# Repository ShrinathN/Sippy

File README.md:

# Sippy
A device which will remind me to drink water. Pretty cool. Uses accelerometer data to predict when, and how much water was drank. Needs the geometry of the bottle it is mounted on to work. WIP.

## Assembled

## Images of the board

## Images of the enclosure

## Renders of the PCB

## Renders of the enclosure

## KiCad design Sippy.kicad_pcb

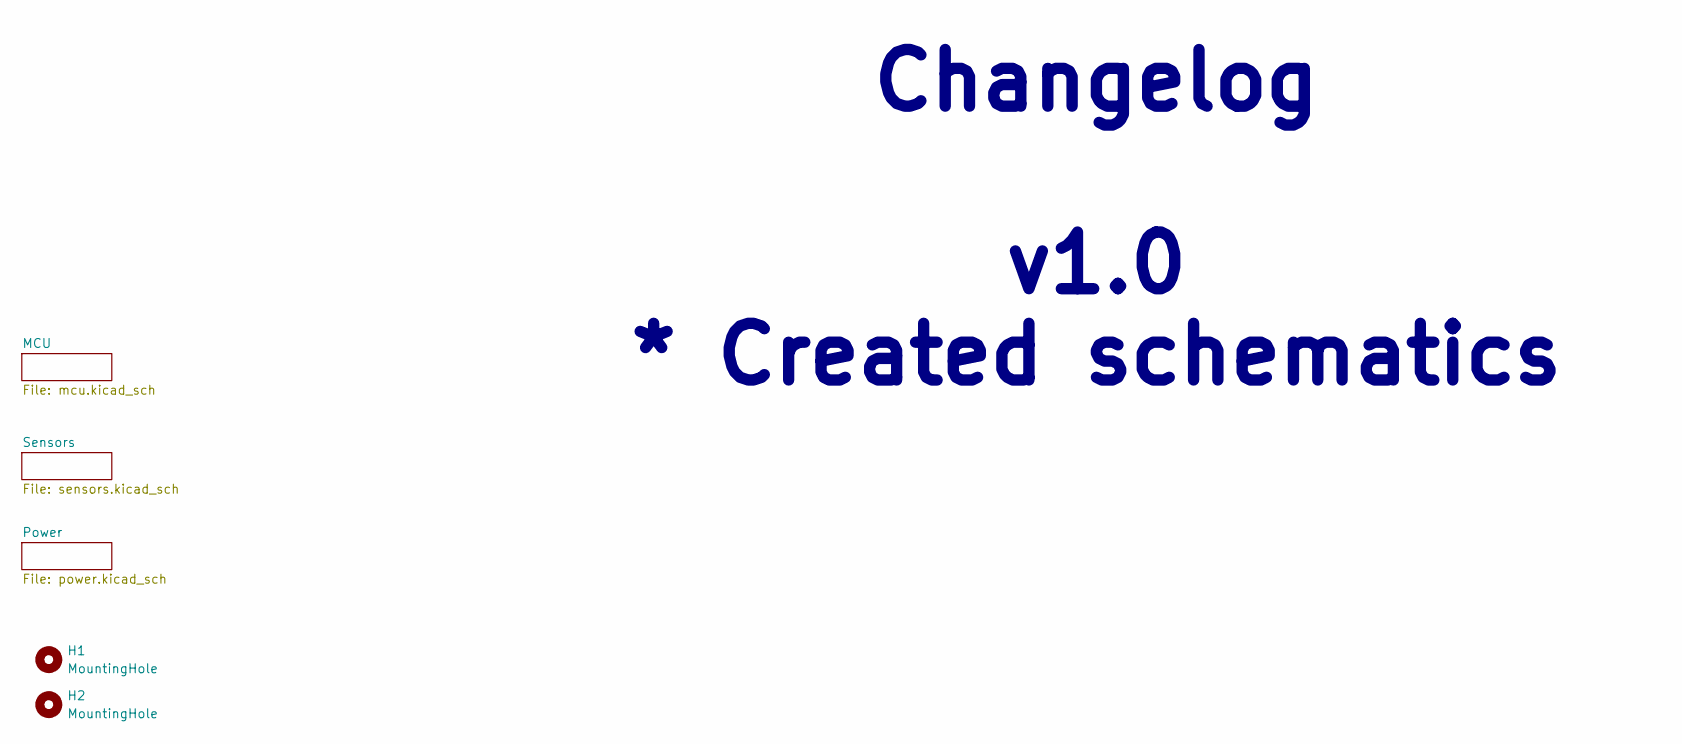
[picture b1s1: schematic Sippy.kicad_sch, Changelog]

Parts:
H1, H2: MountingHole; MountingHole_3.2mm_M3

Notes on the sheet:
Changelog v1.0 * Created schematics

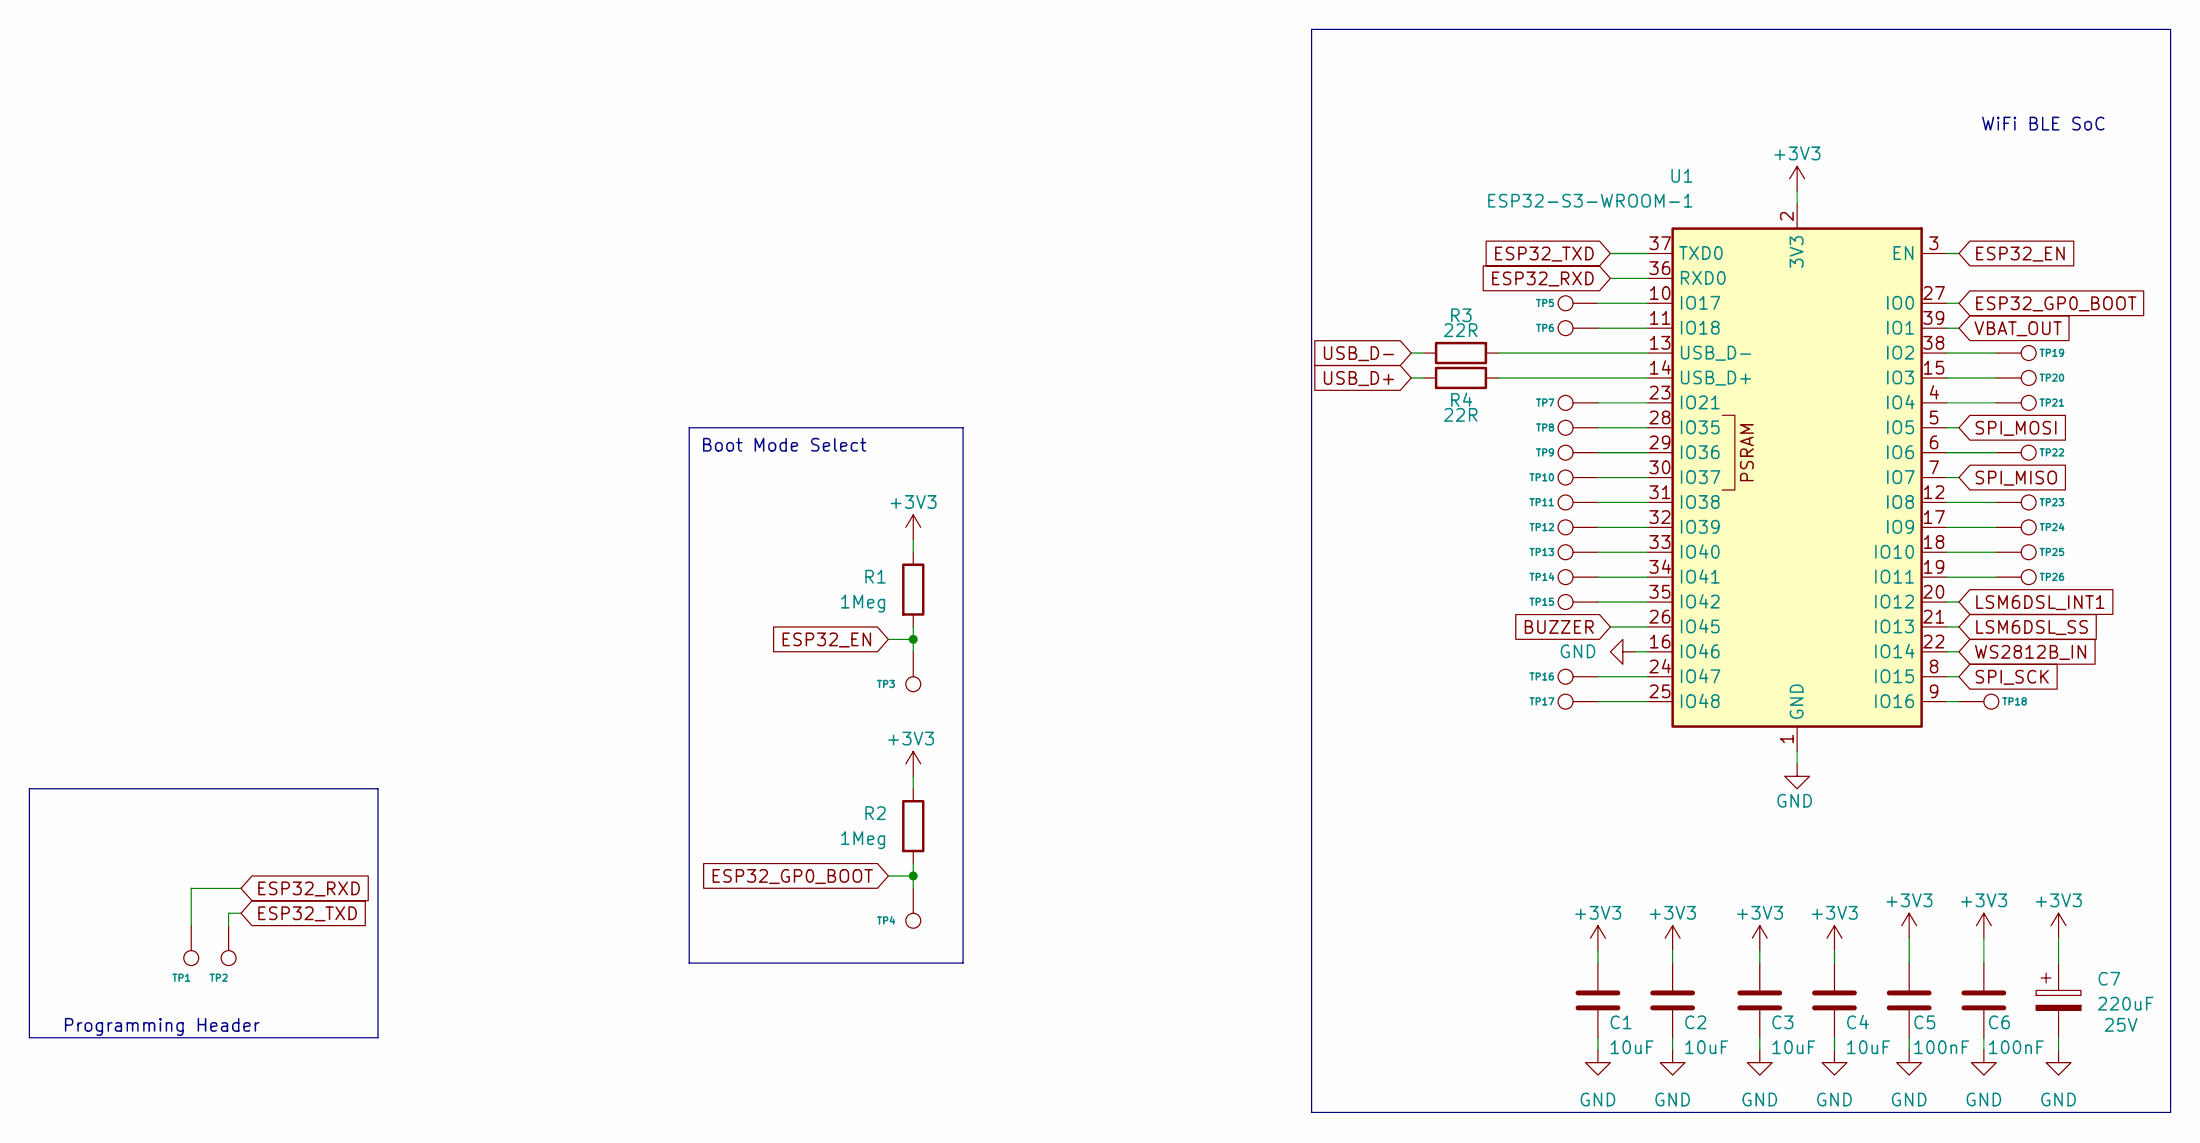
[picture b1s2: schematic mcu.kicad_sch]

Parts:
C1, C2, C3, C4: 10uF; C_0805_2012Metric
C5, C6: 100nF; C_0805_2012Metric
C7: 220uF; CP_Radial_D5.0mm_P2.00mm; Rating 25V
R1, R2: 1Meg; R_0805_2012Metric
R3, R4: 22R; R_0805_2012Metric
TP1, TP2, TP3, TP4, TP5, TP6, TP7, TP8, TP9, TP10, TP11, TP12, TP13, TP14, TP15, TP16, TP17, TP18, TP19, TP20, TP21, TP22, TP23, TP24, TP25, TP26: TestPoint; TestPoint_Pad_D1.0mm_small
U1: ESP32-S3-WROOM-1

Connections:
+3V3: C1.2, C2.2, C3.2, C4.2, C5.2, C6.2, C7.1, R1.1, R2.1, U1.2 (3V3); also elsewhere on the board
BUZZER: U1.26 (IO45); also elsewhere on the board
ESP32_EN: R1.2, TP3.1, U1.3 (EN)
ESP32_GP0_BOOT: R2.2, TP4.1, U1.27 (IO0)
ESP32_RXD: TP1.1, U1.36 (RXD0)
ESP32_TXD: TP2.1, U1.37 (TXD0)
GND: C1.1, C2.1, C3.1, C4.1, C5.1, C6.1, C7.2, U1.1 (GND), U1.16 (IO46), U1.40 (GND), U1.41 (GND); also elsewhere on the board
LSM6DSL_INT1: U1.20 (IO12); also elsewhere on the board
LSM6DSL_SS: U1.21 (IO13); also elsewhere on the board
unnamed: TP19.1, U1.38 (IO2)
unnamed: TP20.1, U1.15 (IO3)
unnamed: TP21.1, U1.4 (IO4)
unnamed: TP22.1, U1.6 (IO6)
unnamed: TP23.1, U1.12 (IO8)
unnamed: TP24.1, U1.17 (IO9)
unnamed: TP25.1, U1.18 (IO10)
unnamed: TP26.1, U1.19 (IO11)
unnamed: TP18.1, U1.9 (IO16)
unnamed: TP5.1, U1.10 (IO17)
unnamed: TP6.1, U1.11 (IO18)
unnamed: TP7.1, U1.23 (IO21)
unnamed: TP8.1, U1.28 (IO35)
unnamed: TP9.1, U1.29 (IO36)
unnamed: TP10.1, U1.30 (IO37)
unnamed: TP11.1, U1.31 (IO38)
unnamed: TP12.1, U1.32 (IO39)
unnamed: TP13.1, U1.33 (IO40)
unnamed: TP14.1, U1.34 (IO41)
unnamed: TP15.1, U1.35 (IO42)
unnamed: TP16.1, U1.24 (IO47)
unnamed: TP17.1, U1.25 (IO48)
unnamed: R4.1, U1.14 (USB_D+)
unnamed: R3.2, U1.13 (USB_D-)
SPI_MISO: U1.7 (IO7); also elsewhere on the board
SPI_MOSI: U1.5 (IO5); also elsewhere on the board
SPI_SCK: U1.8 (IO15); also elsewhere on the board
USB_D+: R4.2; also elsewhere on the board
USB_D-: R3.1; also elsewhere on the board
VBAT_OUT: U1.39 (IO1); also elsewhere on the board
WS2812B_IN: U1.22 (IO14); also elsewhere on the board

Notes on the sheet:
Boot Mode Select
WiFi BLE SoC
Programming Header

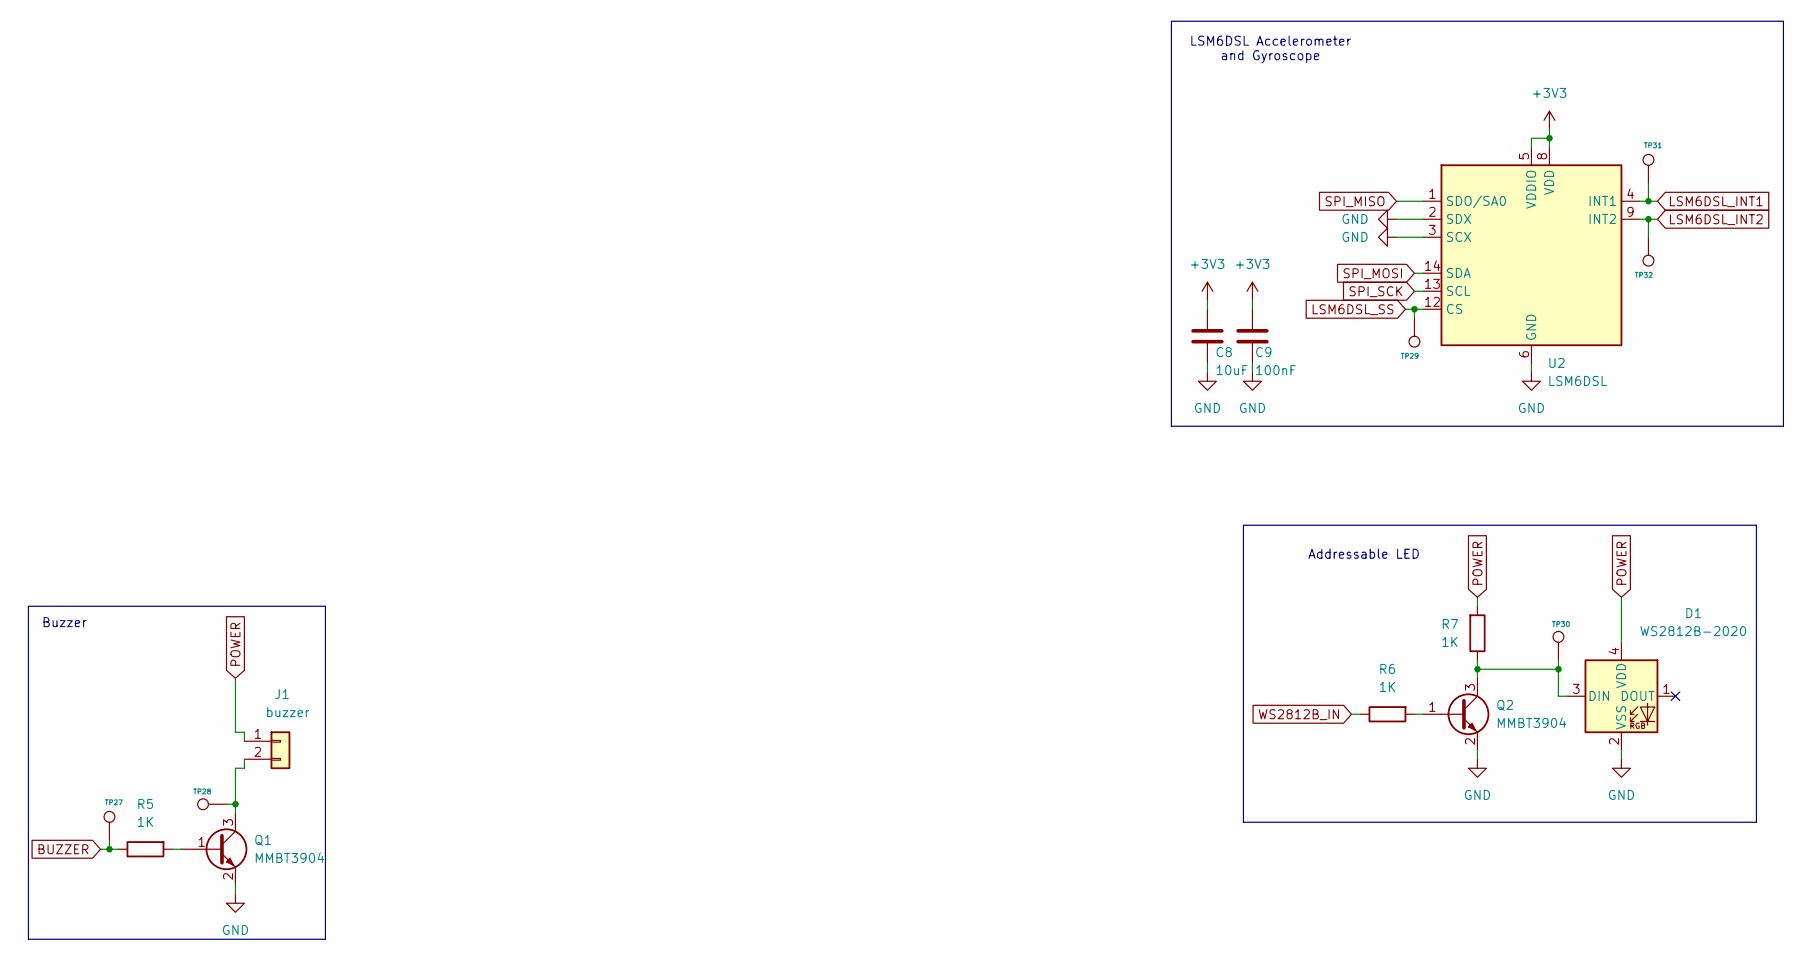
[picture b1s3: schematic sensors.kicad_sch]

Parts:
C8: 10uF; C_0805_2012Metric
C9: 100nF; C_0805_2012Metric
D1: WS2812B-2020; LED_WS2812B-2020_PLCC4_2.0x2.0mm
J1: buzzer; PinHeader_1x02_P2.54mm_Vertical
Q1, Q2: MMBT3904; SOT-23
R5, R6, R7: 1K; R_0805_2012Metric
TP27, TP28, TP29, TP30, TP31, TP32: TestPoint; TestPoint_Pad_D1.0mm_small
U2: LSM6DSL; LGA-14_3x2.5mm_P0.5mm_LayoutBorder3x4y

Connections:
+3V3: C8.2, C9.2, U2.5 (VDDIO), U2.8 (VDD); also elsewhere on the board
BUZZER: R5.1, TP27.1; also elsewhere on the board
GND: C8.1, C9.1, D1.2 (VSS), Q1.2 (E), Q2.2 (E), U2.2 (SDX), U2.3 (SCX), U2.6 (GND), U2.7 (GND); also elsewhere on the board
LSM6DSL_INT1: TP31.1, U2.4 (INT1); also elsewhere on the board
LSM6DSL_INT2: TP32.1, U2.9 (INT2)
LSM6DSL_SS: TP29.1, U2.12 (CS); also elsewhere on the board
unnamed: D1.3 (DIN), Q2.3 (C), R7.1, TP30.1
unnamed: J1.2, Q1.3 (C), TP28.1
unnamed: Q1.1 (B), R5.2
unnamed: Q2.1 (B), R6.2
POWER: D1.4 (VDD), J1.1, R7.2; also elsewhere on the board
SPI_MISO: U2.1 (SDO/SA0); also elsewhere on the board
SPI_MOSI: U2.14 (SDA); also elsewhere on the board
SPI_SCK: U2.13 (SCL); also elsewhere on the board
WS2812B_IN: R6.1; also elsewhere on the board

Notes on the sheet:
Addressable LED
Buzzer
LSM6DSL Accelerometer and Gyroscope

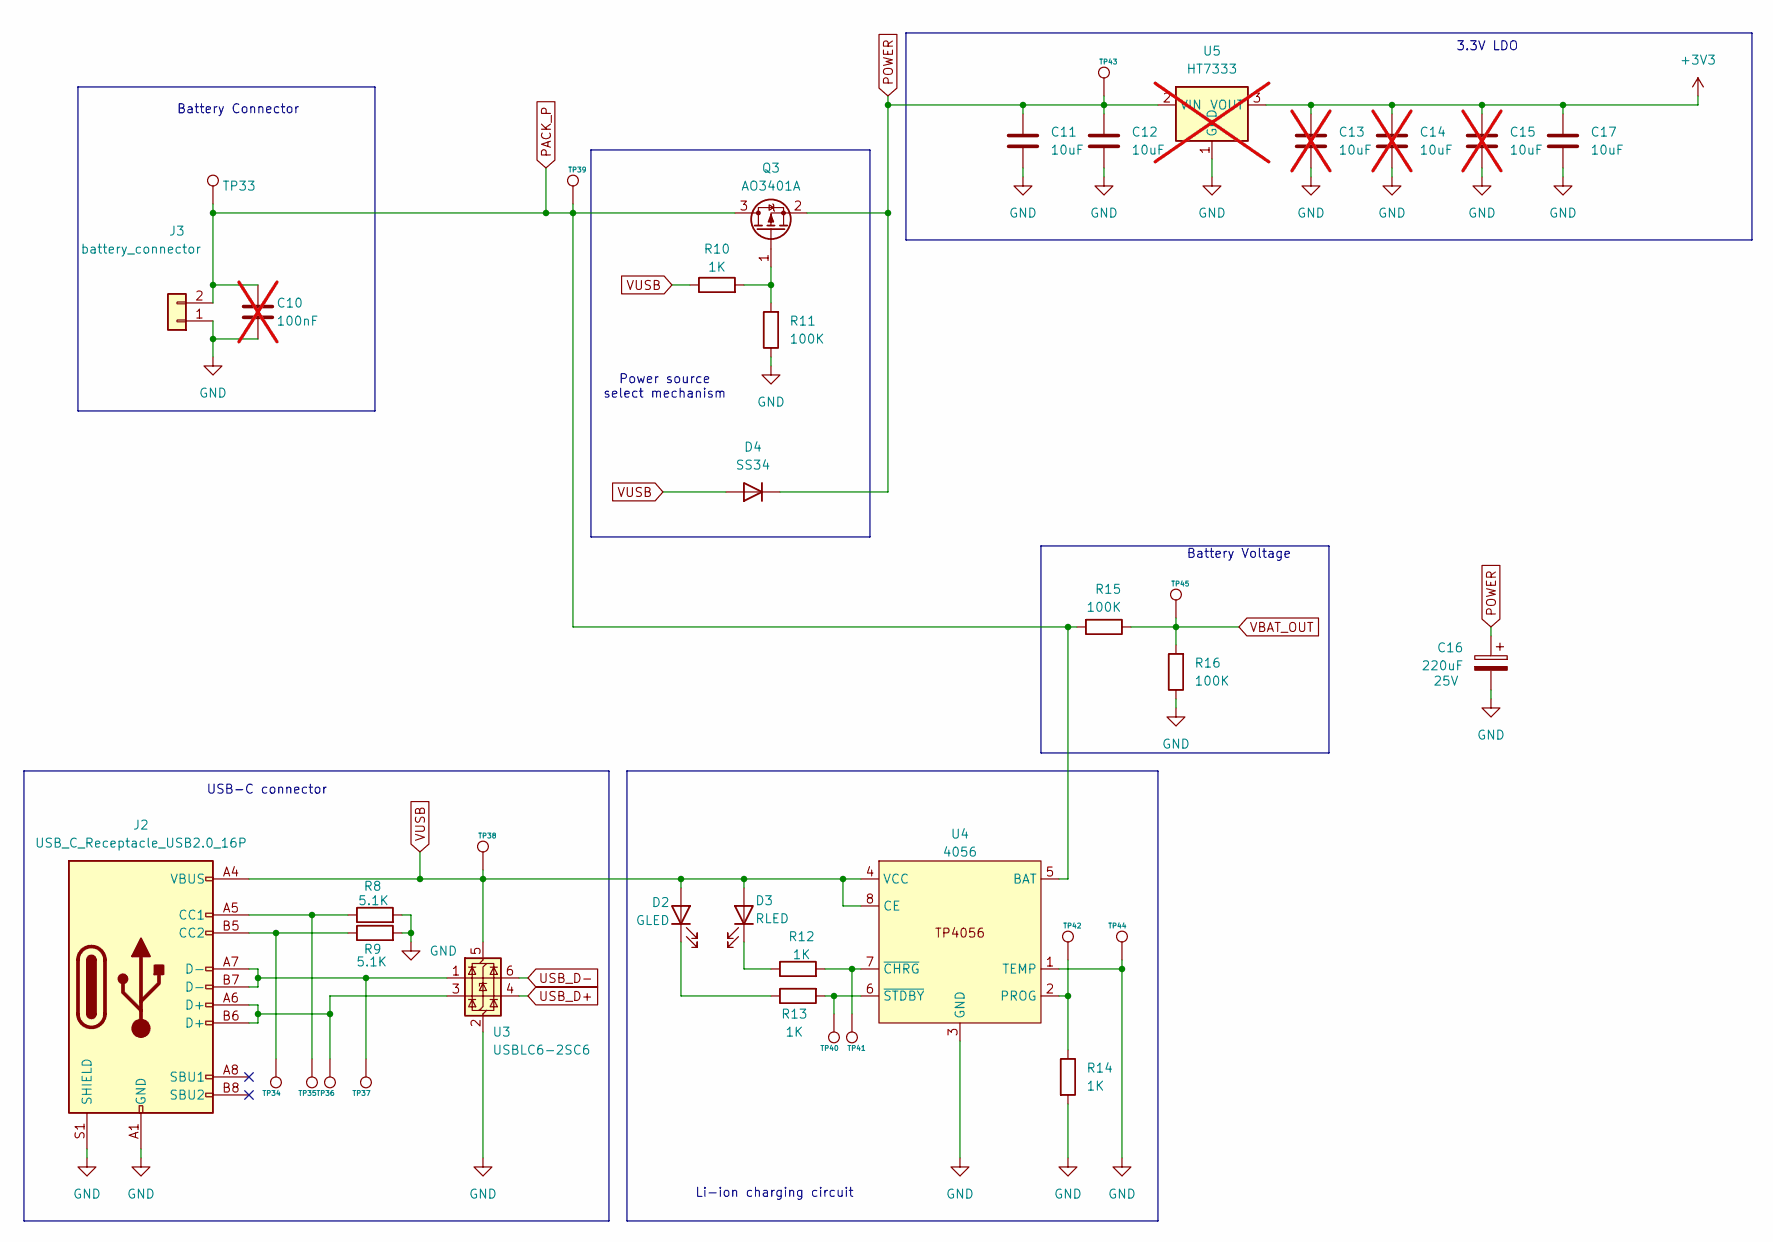
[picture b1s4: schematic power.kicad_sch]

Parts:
C10: 100nF; C_0805_2012Metric; not fitted
C11, C12, C17: 10uF; C_0805_2012Metric
C13, C14, C15: 10uF; C_0805_2012Metric; not fitted
C16: 220uF; CP_Radial_D5.0mm_P2.00mm; Rating 25V
D2: GLED; LED_0805_2012Metric
D3: RLED; LED_0805_2012Metric
D4: SS34; D_SMA
J2: USB_C_Receptacle_USB2.0_16P; USB_C_Receptacle_HRO_TYPE-C-31-M-12
J3: battery_connector; PinHeader_1x02_P2.54mm_Vertical
Q3: AO3401A; SOT-23
R8, R9: 5.1K; R_0805_2012Metric
R10, R12, R13, R14: 1K; R_0805_2012Metric
R11, R15, R16: 100K; R_0805_2012Metric
TP33, TP34, TP35, TP36, TP37, TP38, TP39, TP40, TP41, TP42, TP43, TP44, TP45: TestPoint; TestPoint_Pad_D1.0mm_small
U3: USBLC6-2SC6; SOT-23-6
U4: 4056; SOP-8_3.9x4.9mm_P1.27mm
U5: HT7333; SOT-89-3; not fitted

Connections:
+3V3: C13.1, C14.1, C15.1, C17.1, U5.3 (VOUT); also elsewhere on the board
GND: C10.2, C11.2, C12.2, C13.2, C14.2, C15.2, C16.2, C17.2, J2.A1 (GND), J2.A12 (GND), J2.B1 (GND), J2.B12 (GND), J2.S1 (SHIELD), J3.1, R8.2, R9.2, R11.1, R14.2, R16.1, TP44.1, U3.2 (GND), U4.1 (TEMP), U4.3 (GND), U5.1 (GND); also elsewhere on the board
unnamed: D2.1 (K), R13.1
unnamed: D3.1 (K), R12.1
unnamed: J2.A5 (CC1), R8.1, TP35.1
unnamed: J2.B5 (CC2), R9.1, TP34.1
unnamed: J2.A6 (D+), J2.B6 (D+), TP36.1, U3.3 (I/O2)
unnamed: J2.A7 (D-), J2.B7 (D-), TP37.1, U3.1 (I/O1)
unnamed: Q3.1 (G), R10.2, R11.2
unnamed: R14.1, TP42.1, U4.2 (PROG)
unnamed: R12.2, TP41.1, U4.7 (~CHRG)
unnamed: R13.2, TP40.1, U4.6 (~STDBY)
PACK_P: C10.1, J3.2, Q3.3 (D), R15.2, TP33.1, TP39.1, U4.5 (BAT)
POWER: C11.1, C12.1, C16.1, D4.1 (K), Q3.2 (S), TP43.1, U5.2 (VIN); also elsewhere on the board
USB_D+: U3.4 (I/O2); also elsewhere on the board
USB_D-: U3.6 (I/O1); also elsewhere on the board
VBAT_OUT: R15.1, R16.2, TP45.1; also elsewhere on the board
VUSB: D2.2 (A), D3.2 (A), D4.2 (A), J2.A4 (VBUS), J2.A9 (VBUS), J2.B4 (VBUS), J2.B9 (VBUS), R10.1, TP38.1, U3.5 (VBUS), U4.4 (VCC), U4.8 (CE)

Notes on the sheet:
Battery Connector
Battery Voltage
3.3V LDO
USB-C connector
Li-ion charging circuit
Power source select mechanism

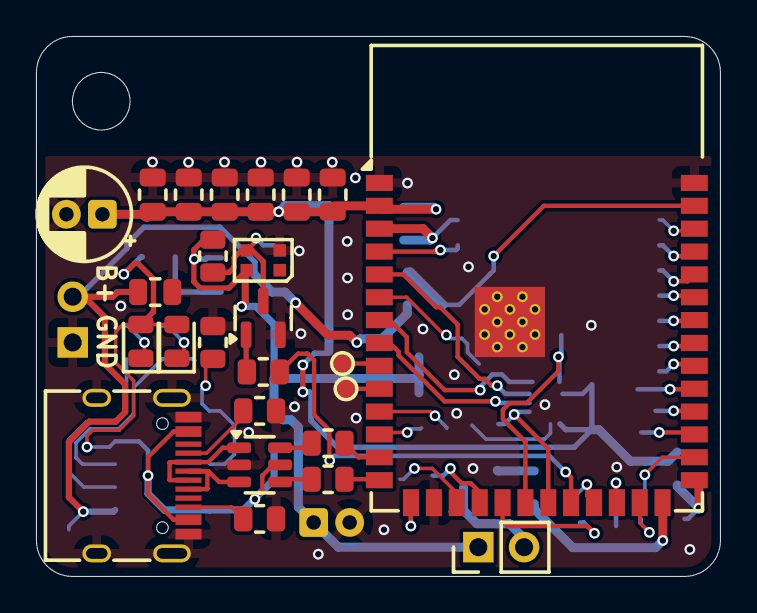
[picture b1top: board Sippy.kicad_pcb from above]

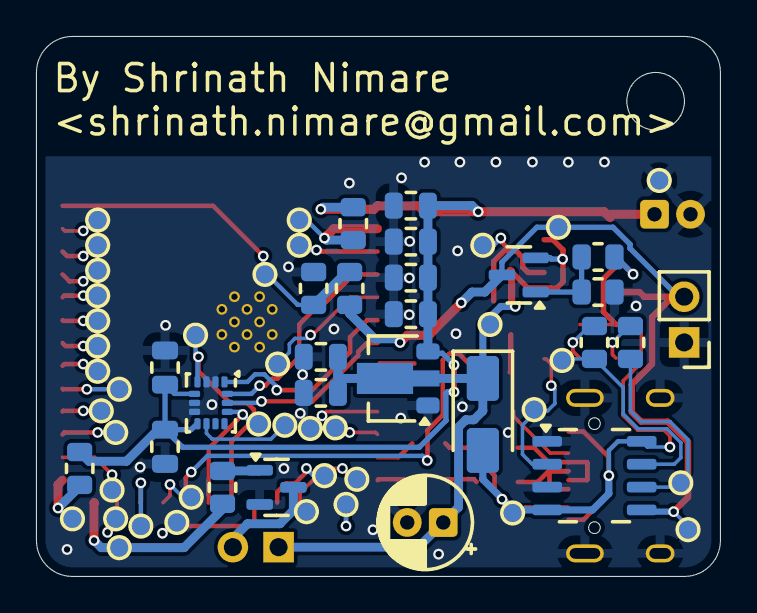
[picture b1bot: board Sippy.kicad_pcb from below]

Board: 2 copper layers, 38.0 x 30.0 mm, 90 parts (64 on the bottom side), 58 nets.

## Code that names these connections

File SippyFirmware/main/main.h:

#ifndef MAIN_H
#define MAIN_H

// common SDK defines
#include <stdio.h>
#include "freertos/FreeRTOS.h"
#include "freertos/task.h"
#include "driver/gpio.h"
#include "esp_sleep.h"
#include "esp_log.h"
#include "nvs_flash.h"
#include "esp_system.h"
#include "esp_wifi.h"
#include "esp_event.h"
#include "esp_sleep.h"

#include "lwip/err.h"
#include "lwip/sys.h"

#include "driver/spi_master.h"
#include "driver/spi_common.h"
#include "esp_adc/adc_oneshot.h"
#include "esp_adc/adc_cali.h"
#include "esp_adc/adc_cali_scheme.h"
#include <stdlib.h>
#include <string.h>
#include "driver/rmt_tx.h"
#include "esp_err.h"

#include <sys/socket.h>
#include <sys/types.h>
#include <netinet/in.h>
#include "freertos/FreeRTOSConfig.h"
/* BLE */
#include "nimble/nimble_port.h"
#include "nimble/nimble_port_freertos.h"
#include "host/ble_hs.h"
#include "host/util/util.h"
#include "console/console.h"
#include "services/gatt/ble_svc_gatt.h"
#include "services/gap/ble_svc_gap.h"

// macros
#define ZEROS { \
    0,          \
}

// ADC pins
#define PIN_VBAT_OUT 1

//SPI Pins
#define PIN_SPI_MISO GPIO_NUM_7
#define PIN_SPI_MOSI GPIO_NUM_5
#define PIN_SPI_SCK GPIO_NUM_15
#define PIN_LSM6DSL_SS GPIO_NUM_13
#define PIN_LSM6DSL_INT1 GPIO_NUM_12
#define PIN_BUZZER GPIO_NUM_45
#define PIN_LED_DOUT GPIO_NUM_14

#endif

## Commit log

2025-10-27 Added files
2025-10-27 Removed extra files
2025-10-27 Added pics
2025-10-27 Added enclosure renders
